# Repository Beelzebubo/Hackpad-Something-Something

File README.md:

# Hackpad-Something-Something

This is a hardware project i.e. creating a macropad from scratch. 
My macropad in particular features a 12 key arrangement in a 4 column 3 row format. 
I used the SW_CHERRY_MX 1u as my mechanical keyboard switch and the 1N4148 diode connected to Module Seeduino xiao which acts as my microcontroller.

The Schematic of the project is given below.

Based on the Schematic I created the PCB design. 

The total dimension of the PCB came out to be 99.552*91.0 mm 
Using the PCB as base I created the case to enclose the hackpad.

# Firmware
For the firmware I used KMK instead of the other popular ones. This decision was mostly because of my comfort in python and ease and simple to write code of KMK.

# Final design of the macropad

I used FreeCAD for the design of the macropad's case and it was not fun. I searched tutorials and it only existed for other stuff so I looked at the other stuff's tutorial and applied it to the macropad.
The final design is well not the best to be frank but I made it myself so I am quite proud of it. 

# BOM

Now then here should be everything required to make this yourself:

1. 12× Cherry MX Switches
2. 12× DSA Keycaps
3. 12× 1N4148 SOD-123 Diodes
4. 1× Xiao RP2040
5. 4× M2 × 6mm SHCS Bolts (Corner Screws)
6. Case (2 part case Top and Bottom)
7. Soldering iron + solder
8. Wire cutters

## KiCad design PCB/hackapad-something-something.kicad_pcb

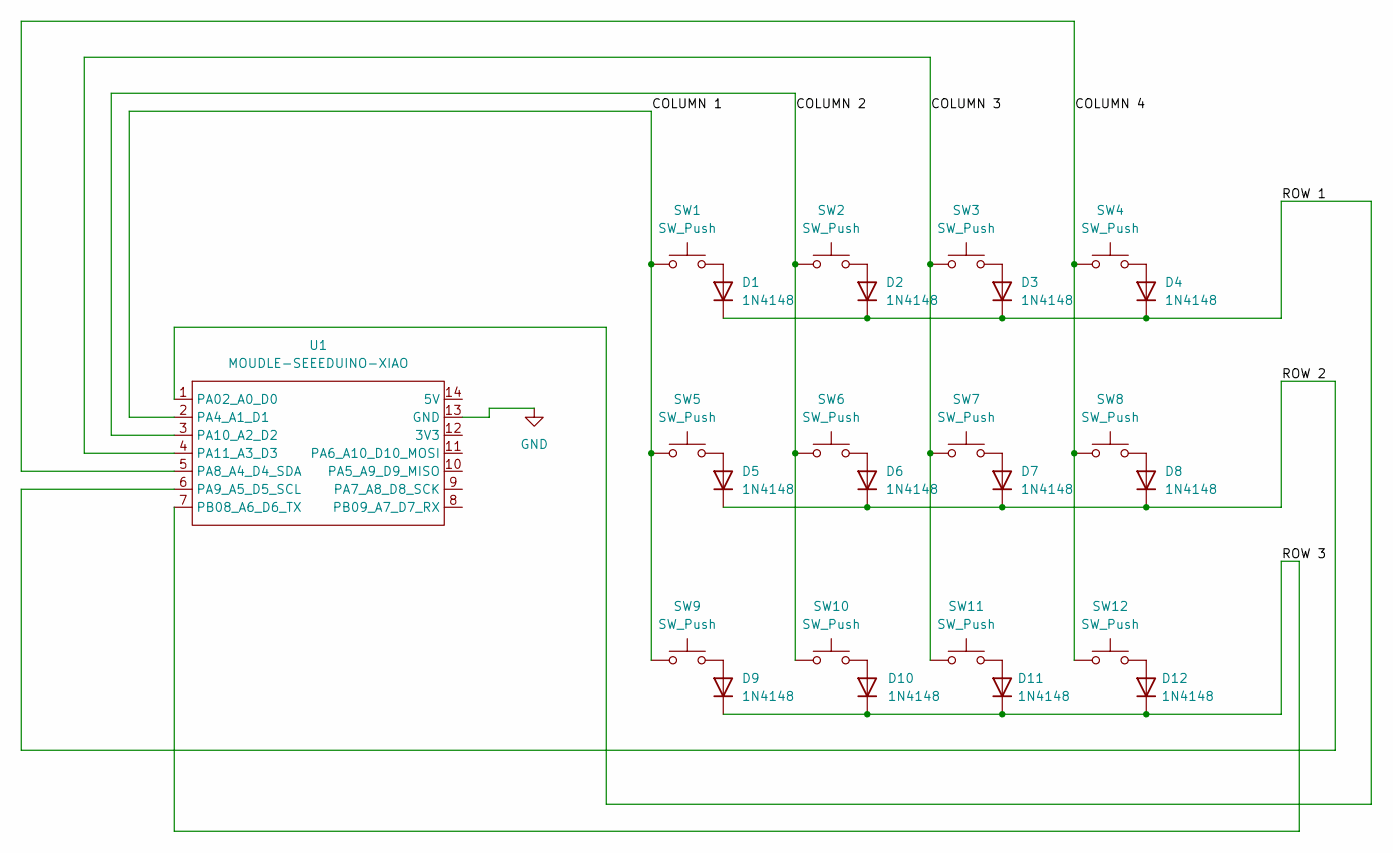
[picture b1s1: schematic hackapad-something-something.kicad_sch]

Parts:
D1, D2, D3, D4, D5, D6, D7, D8, D9, D10, D11, D12: 1N4148; D_SOD-123
SW1, SW2, SW3, SW4, SW5, SW6, SW7, SW8, SW9, SW10, SW11, SW12: SW_Push; SW_Cherry_MX_1.00u_PCB
U1: MOUDLE-SEEEDUINO-XIAO; XIAO-Generic-Hybrid-14P-2.54-21X17.8MM

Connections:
/COLUMN 1: SW1.1, SW5.1, SW9.1, U1.2 (PA4_A1_D1)
/COLUMN 2: SW2.1, SW6.1, SW10.1, U1.3 (PA10_A2_D2)
/COLUMN 3: SW3.1, SW7.1, SW11.1, U1.4 (PA11_A3_D3)
/COLUMN 4: SW4.1, SW8.1, SW12.1, U1.5 (PA8_A4_D4_SDA)
/ROW 1: D1.1 (K), D2.1 (K), D3.1 (K), D4.1 (K), U1.1 (PA02_A0_D0)
/ROW 2: D5.1 (K), D6.1 (K), D7.1 (K), D8.1 (K), U1.6 (PA9_A5_D5_SCL)
/ROW 3: D9.1 (K), D10.1 (K), D11.1 (K), D12.1 (K), U1.7 (PB08_A6_D6_TX)
GND: U1.13 (GND)
unnamed: D1.2 (A), SW1.2
unnamed: D2.2 (A), SW2.2
unnamed: D3.2 (A), SW3.2
unnamed: D4.2 (A), SW4.2
unnamed: D5.2 (A), SW5.2
unnamed: D6.2 (A), SW6.2
unnamed: D7.2 (A), SW7.2
unnamed: D8.2 (A), SW8.2
unnamed: D9.2 (A), SW9.2
unnamed: D10.2 (A), SW10.2
unnamed: D11.2 (A), SW11.2
unnamed: D12.2 (A), SW12.2

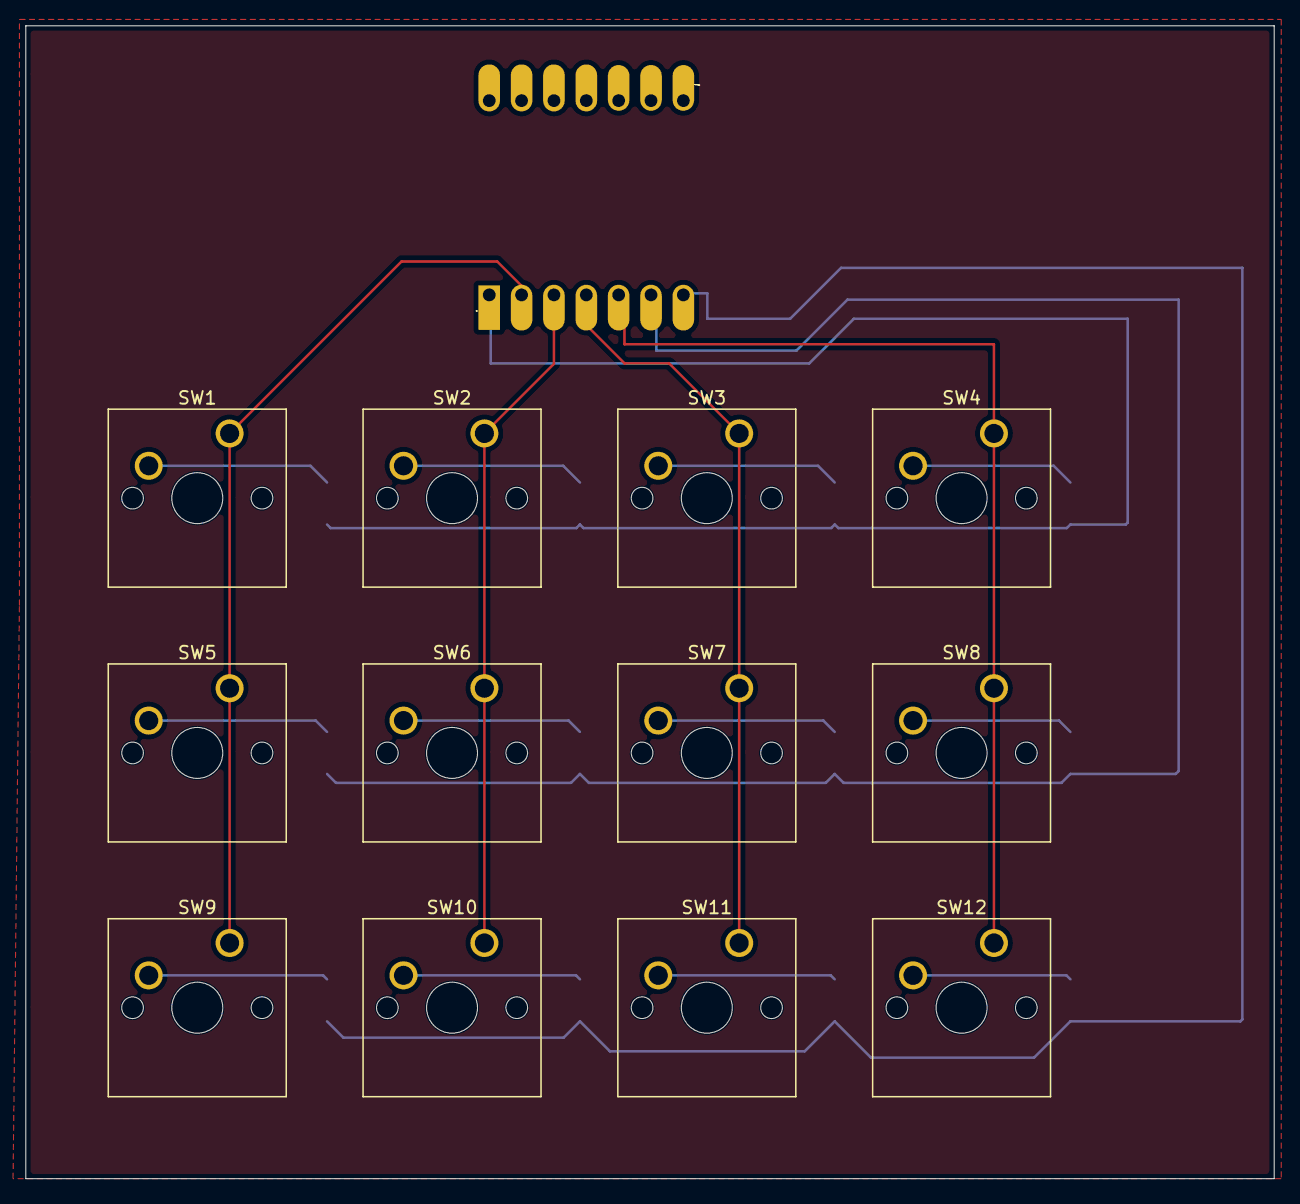
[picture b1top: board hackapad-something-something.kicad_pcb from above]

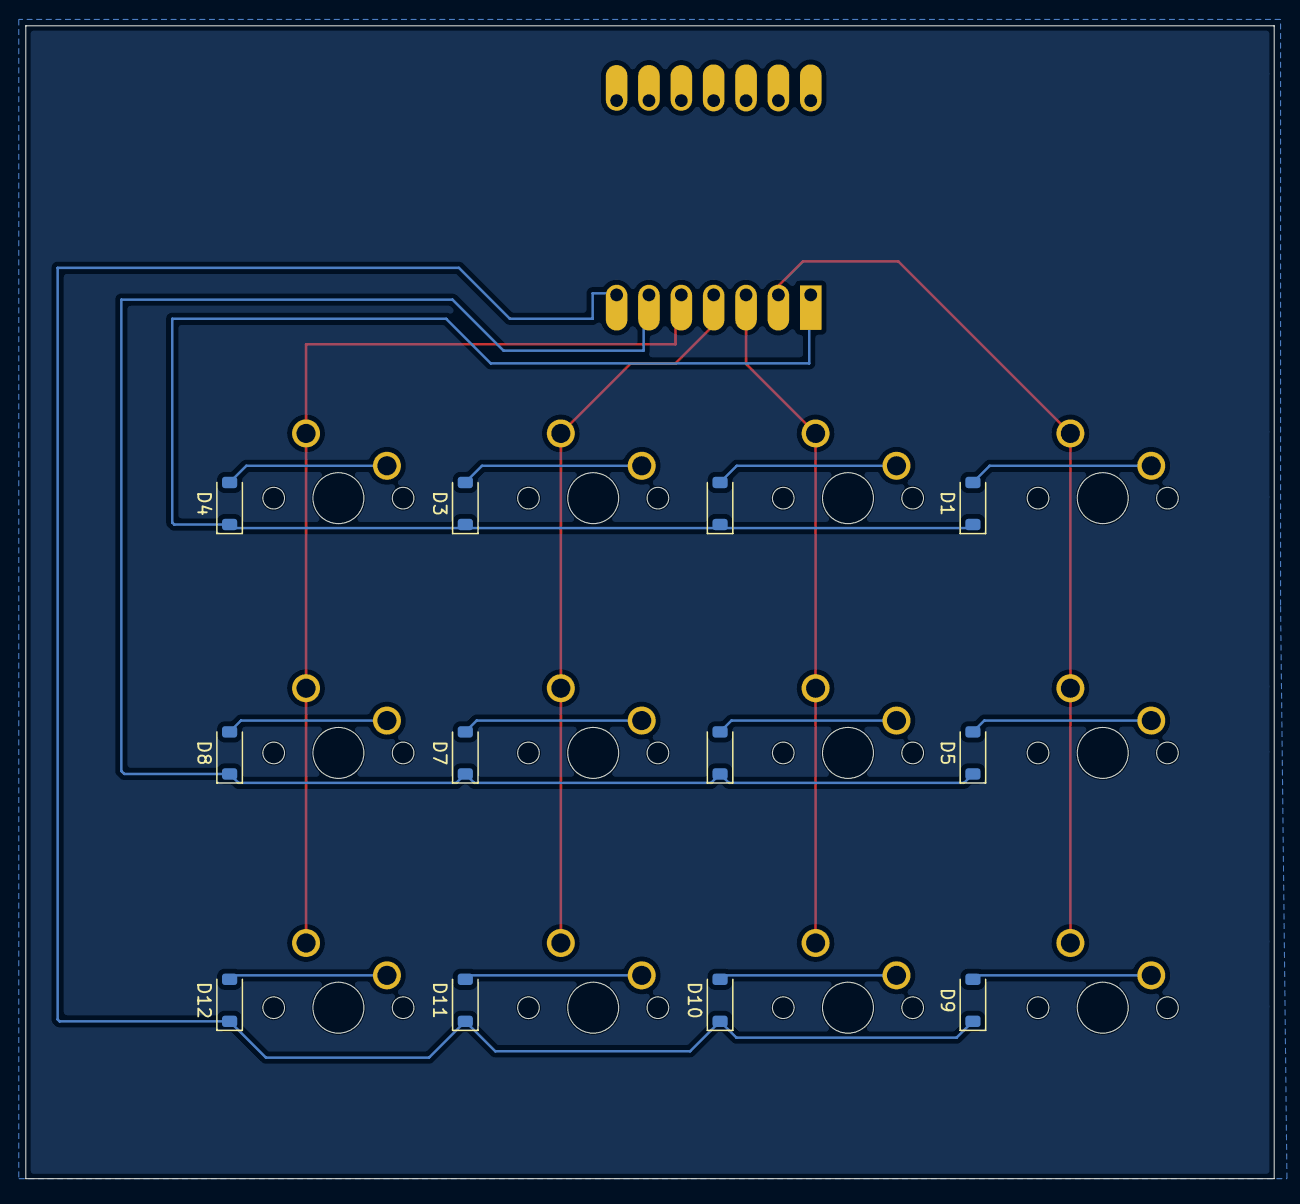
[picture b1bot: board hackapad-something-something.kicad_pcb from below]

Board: 2 copper layers, 98.0 x 90.5 mm, 25 parts (12 on the bottom side), 19 nets.
